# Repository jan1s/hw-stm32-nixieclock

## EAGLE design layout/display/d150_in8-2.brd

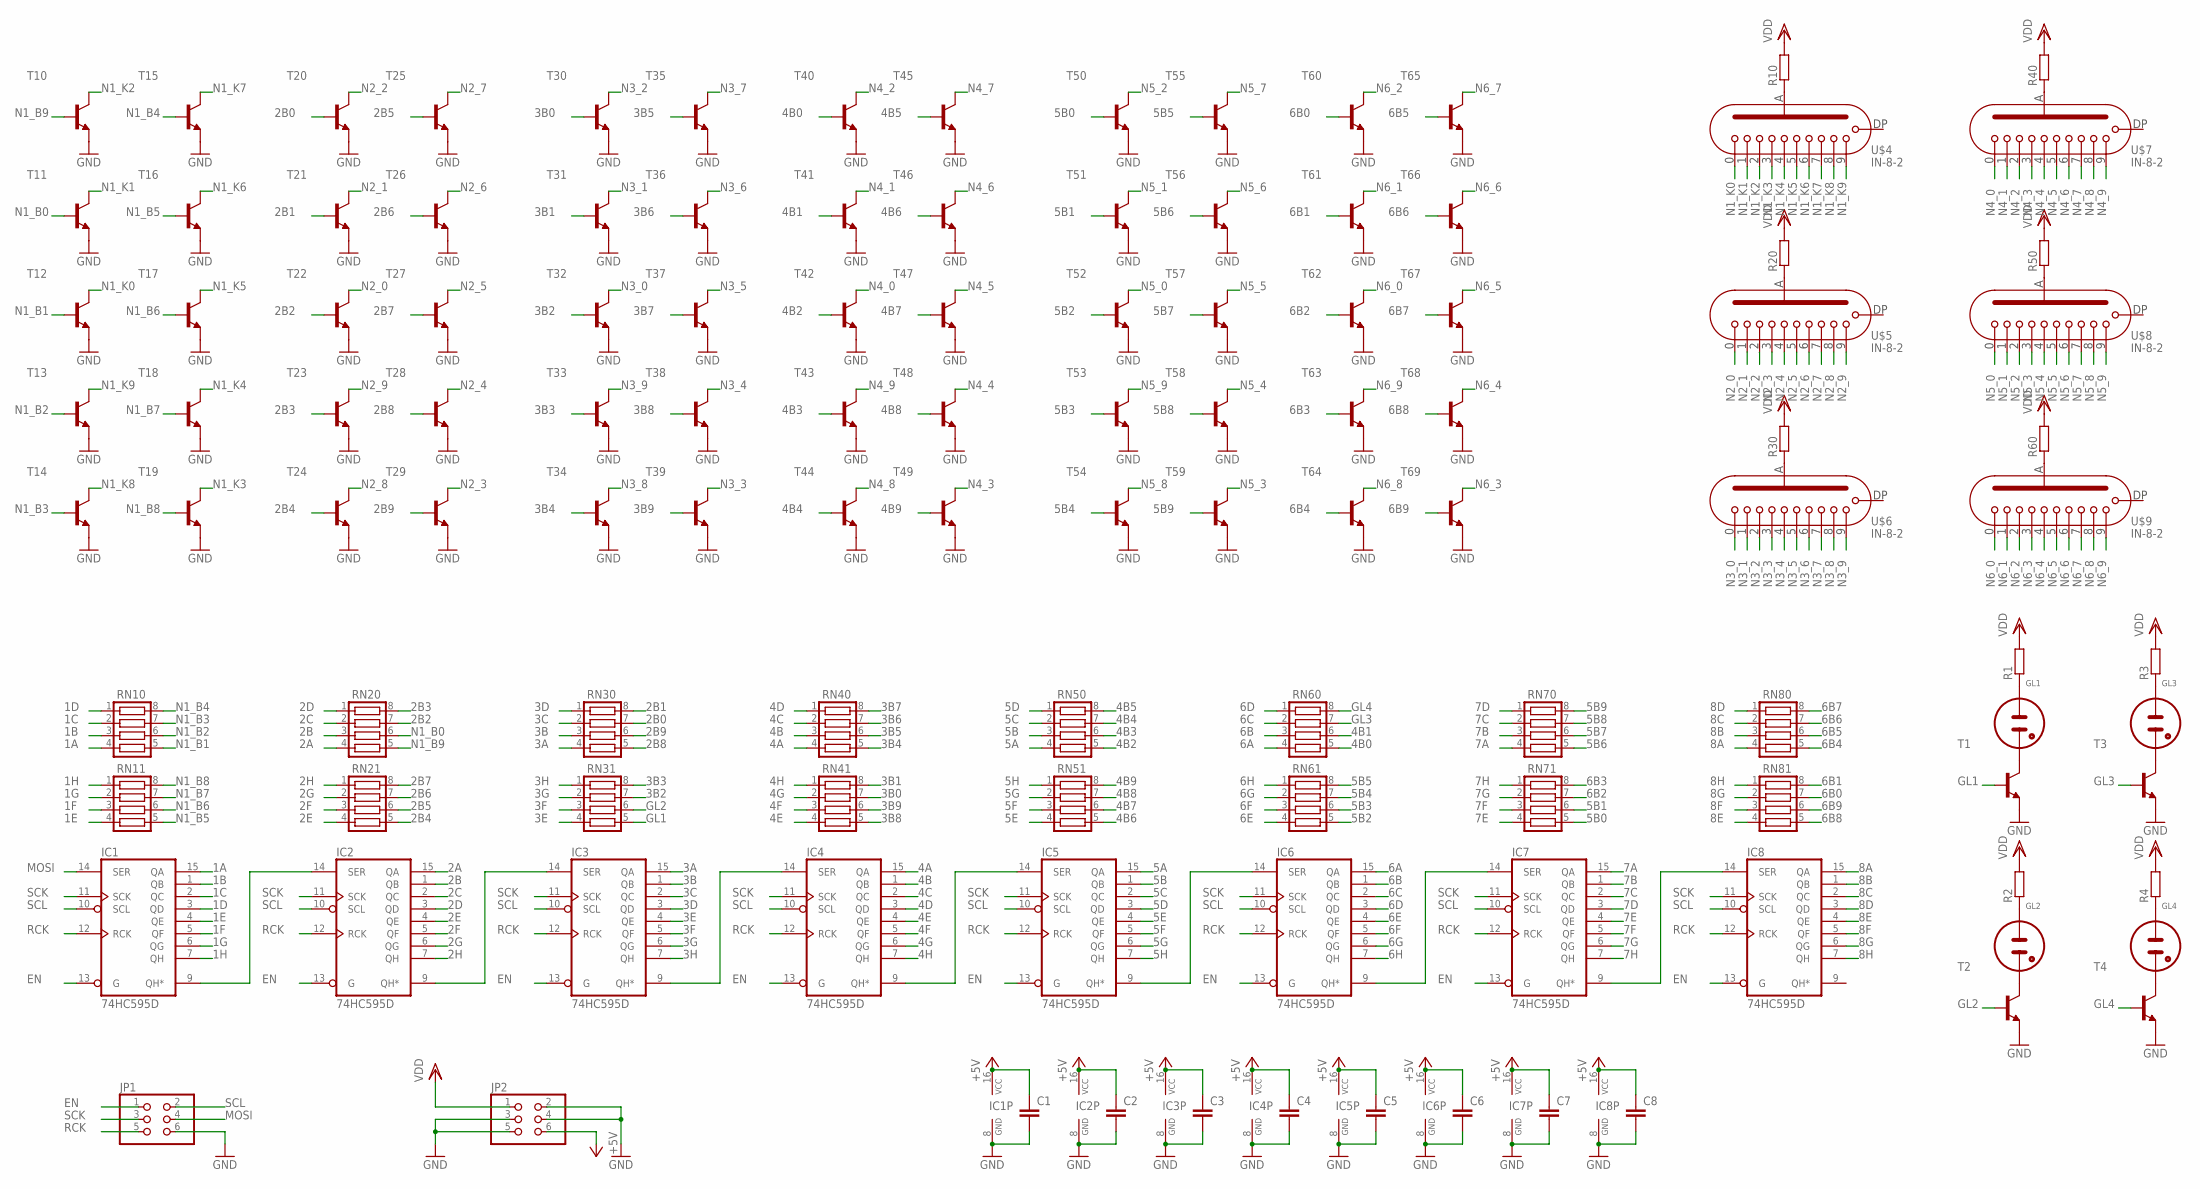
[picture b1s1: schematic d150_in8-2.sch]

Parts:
C1, C2, C3, C4, C5, C6, C7, C8: C-EUC0603; C0603
GL1, GL2, GL3, GL4: NE2-NEON-BULB-DRILL
IC1, IC2, IC3, IC4, IC5, IC6, IC7, IC8: 74HC595D; SO16
JP1, JP2: PINHD-2X3_2.54-SMD; 2X03SMD
R1, R2, R3, R4, R10, R20, R30, R40, R50, R60: R-EU_R0603; R0603
RN10, RN11, RN20, RN21, RN30, RN31, RN40, RN41, RN50, RN51, RN60, RN61, RN70, RN71, RN80, RN81: CTS742C083
T1, T2, T3, T4, T10, T11, T12, T13, T14, T15, T16, T17, T18, T19, T20, T21, T22, T23, T24, T25, T26, T27, T28, T29, T30, T31, T32, T33, T34, T35, T36, T37, T38, T39, T40, T41, T42, T43, T44, T45, T46, T47, T48, T49, T50, T51, T52, T53, T54, T55, T56, T57, T58, T59, T60, T61, T62, T63, T64, T65, T66, T67, T68, T69: SMBTA42; SOT23
U$4, U$5, U$6, U$7, U$8, U$9: IN-8-2

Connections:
1A: IC1.15 (QA), RN10.4
1B: IC1.1 (QB), RN10.3
1C: IC1.2 (QC), RN10.2
1D: IC1.3 (QD), RN10.1
1E: IC1.4 (QE), RN11.4
1F: IC1.5 (QF), RN11.3
1G: IC1.6 (QG), RN11.2
1H: IC1.7 (QH), RN11.1
2A: IC2.15 (QA), RN20.4
2B: IC2.1 (QB), RN20.3
2B0: RN30.7, T20.1 (B)
2B1: RN30.8, T21.1 (B)
2B2: RN20.7, T22.1 (B)
2B3: RN20.8, T23.1 (B)
2B4: RN21.5, T24.1 (B)
2B5: RN21.6, T25.1 (B)
2B6: RN21.7, T26.1 (B)
2B7: RN21.8, T27.1 (B)
2B8: RN30.5, T28.1 (B)
2B9: RN30.6, T29.1 (B)
2C: IC2.2 (QC), RN20.2
2D: IC2.3 (QD), RN20.1
2E: IC2.4 (QE), RN21.4
2F: IC2.5 (QF), RN21.3
2G: IC2.6 (QG), RN21.2
2H: IC2.7 (QH), RN21.1
3A: IC3.15 (QA), RN30.4
3B: IC3.1 (QB), RN30.3
3B0: RN41.7, T30.1 (B)
3B1: RN41.8, T31.1 (B)
3B2: RN31.7, T32.1 (B)
3B3: RN31.8, T33.1 (B)
3B4: RN40.5, T34.1 (B)
3B5: RN40.6, T35.1 (B)
3B6: RN40.7, T36.1 (B)
3B7: RN40.8, T37.1 (B)
3B8: RN41.5, T38.1 (B)
3B9: RN41.6, T39.1 (B)
3C: IC3.2 (QC), RN30.2
3D: IC3.3 (QD), RN30.1
3E: IC3.4 (QE), RN31.4
3F: IC3.5 (QF), RN31.3
3G: IC3.6 (QG), RN31.2
3H: IC3.7 (QH), RN31.1
4A: IC4.15 (QA), RN40.4
4B: IC4.1 (QB), RN40.3
4B0: RN60.5, T40.1 (B)
4B1: RN60.6, T41.1 (B)
4B2: RN50.5, T42.1 (B)
4B3: RN50.6, T43.1 (B)
4B4: RN50.7, T44.1 (B)
4B5: RN50.8, T45.1 (B)
4B6: RN51.5, T46.1 (B)
4B7: RN51.6, T47.1 (B)
4B8: RN51.7, T48.1 (B)
4B9: RN51.8, T49.1 (B)
4C: IC4.2 (QC), RN40.2
4D: IC4.3 (QD), RN40.1
4E: IC4.4 (QE), RN41.4
4F: IC4.5 (QF), RN41.3
4G: IC4.6 (QG), RN41.2
4H: IC4.7 (QH), RN41.1
5A: IC5.15 (QA), RN50.4
5B: IC5.1 (QB), RN50.3
5B0: RN71.5, T50.1 (B)
5B1: RN71.6, T51.1 (B)
5B2: RN61.5, T52.1 (B)
5B3: RN61.6, T53.1 (B)
5B4: RN61.7, T54.1 (B)
5B5: RN61.8, T55.1 (B)
5B6: RN70.5, T56.1 (B)
5B7: RN70.6, T57.1 (B)
5B8: RN70.7, T58.1 (B)
5B9: RN70.8, T59.1 (B)
5C: IC5.2 (QC), RN50.2
5D: IC5.3 (QD), RN50.1
5E: IC5.4 (QE), RN51.4
5F: IC5.5 (QF), RN51.3
5G: IC5.6 (QG), RN51.2
5H: IC5.7 (QH), RN51.1
6A: IC6.15 (QA), RN60.4
6B: IC6.1 (QB), RN60.3
6B0: RN81.7, T60.1 (B)
6B1: RN81.8, T61.1 (B)
6B2: RN71.7, T62.1 (B)
6B3: RN71.8, T63.1 (B)
6B4: RN80.5, T64.1 (B)
6B5: RN80.6, T65.1 (B)
6B6: RN80.7, T66.1 (B)
6B7: RN80.8, T67.1 (B)
6B8: RN81.5, T68.1 (B)
6B9: RN81.6, T69.1 (B)
6C: IC6.2 (QC), RN60.2
6D: IC6.3 (QD), RN60.1
6E: IC6.4 (QE), RN61.4
6F: IC6.5 (QF), RN61.3
6G: IC6.6 (QG), RN61.2
6H: IC6.7 (QH), RN61.1
7A: IC7.15 (QA), RN70.4
7B: IC7.1 (QB), RN70.3
7C: IC7.2 (QC), RN70.2
7D: IC7.3 (QD), RN70.1
7E: IC7.4 (QE), RN71.4
7F: IC7.5 (QF), RN71.3
7G: IC7.6 (QG), RN71.2
7H: IC7.7 (QH), RN71.1
8A: IC8.15 (QA), RN80.4
8B: IC8.1 (QB), RN80.3
8C: IC8.2 (QC), RN80.2
8D: IC8.3 (QD), RN80.1
8E: IC8.4 (QE), RN81.4
8F: IC8.5 (QF), RN81.3
8G: IC8.6 (QG), RN81.2
8H: IC8.7 (QH), RN81.1
+5V: C1.1, C2.1, C3.1, C4.1, C5.1, C6.1, C7.1, C8.1, IC1.16 (VCC), IC2.16 (VCC), IC3.16 (VCC), IC4.16 (VCC), IC5.16 (VCC), IC6.16 (VCC), IC7.16 (VCC), IC8.16 (VCC), JP2.6
EN: IC1.13 (G), IC2.13 (G), IC3.13 (G), IC4.13 (G), IC5.13 (G), IC6.13 (G), IC7.13 (G), IC8.13 (G), JP1.1
GL1: RN31.5, T1.1 (B)
GL2: RN31.6, T2.1 (B)
GL3: RN60.7, T3.1 (B)
GL4: RN60.8, T4.1 (B)
GND: C1.2, C2.2, C3.2, C4.2, C5.2, C6.2, C7.2, C8.2, IC1.8 (GND), IC2.8 (GND), IC3.8 (GND), IC4.8 (GND), IC5.8 (GND), IC6.8 (GND), IC7.8 (GND), IC8.8 (GND), JP1.6, JP2.2, JP2.3, JP2.4, JP2.5, T1.2 (E), T2.2 (E), T3.2 (E), T4.2 (E), T10.2 (E), T11.2 (E), T12.2 (E), T13.2 (E), T14.2 (E), T15.2 (E), T16.2 (E), T17.2 (E), T18.2 (E), T19.2 (E), T20.2 (E), T21.2 (E), T22.2 (E), T23.2 (E), T24.2 (E), T25.2 (E), T26.2 (E), T27.2 (E), T28.2 (E), T29.2 (E), T30.2 (E), T31.2 (E), T32.2 (E), T33.2 (E), T34.2 (E), T35.2 (E), T36.2 (E), T37.2 (E), T38.2 (E), T39.2 (E), T40.2 (E), T41.2 (E), T42.2 (E), T43.2 (E), T44.2 (E), T45.2 (E), T46.2 (E), T47.2 (E), T48.2 (E), T49.2 (E), T50.2 (E), T51.2 (E), T52.2 (E), T53.2 (E), T54.2 (E), T55.2 (E), T56.2 (E), T57.2 (E), T58.2 (E), T59.2 (E), T60.2 (E), T61.2 (E), T62.2 (E), T63.2 (E), T64.2 (E), T65.2 (E), T66.2 (E), T67.2 (E), T68.2 (E), T69.2 (E)
MOSI: IC1.14 (SER), JP1.4
N1_B0: RN20.6, T11.1 (B)
N1_B1: RN10.5, T12.1 (B)
N1_B2: RN10.6, T13.1 (B)
N1_B3: RN10.7, T14.1 (B)
N1_B4: RN10.8, T15.1 (B)
N1_B5: RN11.5, T16.1 (B)
N1_B6: RN11.6, T17.1 (B)
N1_B7: RN11.7, T18.1 (B)
N1_B8: RN11.8, T19.1 (B)
N1_B9: RN20.5, T10.1 (B)
N1_K0: T12.3 (C), U$4.0
N1_K1: T11.3 (C), U$4.1
N1_K2: T10.3 (C), U$4.2
N1_K3: T19.3 (C), U$4.3
N1_K4: T18.3 (C), U$4.4
N1_K5: T17.3 (C), U$4.5
N1_K6: T16.3 (C), U$4.6
N1_K7: T15.3 (C), U$4.7
N1_K8: T14.3 (C), U$4.8
N1_K9: T13.3 (C), U$4.9
N2_0: T22.3 (C), U$5.0
N2_1: T21.3 (C), U$5.1
N2_2: T20.3 (C), U$5.2
N2_3: T29.3 (C), U$5.3
N2_4: T28.3 (C), U$5.4
N2_5: T27.3 (C), U$5.5
N2_6: T26.3 (C), U$5.6
N2_7: T25.3 (C), U$5.7
N2_8: T24.3 (C), U$5.8
N2_9: T23.3 (C), U$5.9
N3_0: T32.3 (C), U$6.0
N3_1: T31.3 (C), U$6.1
N3_2: T30.3 (C), U$6.2
N3_3: T39.3 (C), U$6.3
N3_4: T38.3 (C), U$6.4
N3_5: T37.3 (C), U$6.5
N3_6: T36.3 (C), U$6.6
N3_7: T35.3 (C), U$6.7
N3_8: T34.3 (C), U$6.8
N3_9: T33.3 (C), U$6.9
N4_0: T42.3 (C), U$7.0
N4_1: T41.3 (C), U$7.1
N4_2: T40.3 (C), U$7.2
N4_3: T49.3 (C), U$7.3
N4_4: T48.3 (C), U$7.4
N4_5: T47.3 (C), U$7.5
N4_6: T46.3 (C), U$7.6
N4_7: T45.3 (C), U$7.7
N4_8: T44.3 (C), U$7.8
N4_9: T43.3 (C), U$7.9
N5_0: T52.3 (C), U$8.0
N5_1: T51.3 (C), U$8.1
N5_2: T50.3 (C), U$8.2
N5_3: T59.3 (C), U$8.3
N5_4: T58.3 (C), U$8.4
N5_5: T57.3 (C), U$8.5
N5_6: T56.3 (C), U$8.6
N5_7: T55.3 (C), U$8.7
N5_8: T54.3 (C), U$8.8
N5_9: T53.3 (C), U$8.9
N6_0: T62.3 (C), U$9.0
N6_1: T61.3 (C), U$9.1
N6_2: T60.3 (C), U$9.2
N6_3: T69.3 (C), U$9.3
N6_4: T68.3 (C), U$9.4
N6_5: T67.3 (C), U$9.5
N6_6: T66.3 (C), U$9.6
N6_7: T65.3 (C), U$9.7
N6_8: T64.3 (C), U$9.8
N6_9: T63.3 (C), U$9.9
unnamed: GL2.1 (A), R2.1
unnamed: GL3.1 (A), R3.1
unnamed: GL4.1 (A), R4.1
unnamed: R10.1, U$4.A (A1)
unnamed: GL2.2 (A1), T2.3 (C)
unnamed: GL1.2 (A1), T1.3 (C)
unnamed: GL4.2 (A1), T4.3 (C)
unnamed: GL3.2 (A1), T3.3 (C)
unnamed: R20.1, U$5.A (A1)
unnamed: IC1.9 (QH*), IC2.14 (SER)
unnamed: IC2.9 (QH*), IC3.14 (SER)
unnamed: IC3.9 (QH*), IC4.14 (SER)
unnamed: R30.1, U$6.A (A1)
unnamed: R40.1, U$7.A (A1)
unnamed: R50.1, U$8.A (A1)
unnamed: IC4.9 (QH*), IC5.14 (SER)
unnamed: R60.1, U$9.A (A1)
unnamed: IC5.9 (QH*), IC6.14 (SER)
unnamed: IC6.9 (QH*), IC7.14 (SER)
unnamed: IC7.9 (QH*), IC8.14 (SER)
unnamed: GL1.1 (A), R1.1
RCK: IC1.12 (RCK), IC2.12 (RCK), IC3.12 (RCK), IC4.12 (RCK), IC5.12 (RCK), IC6.12 (RCK), IC7.12 (RCK), IC8.12 (RCK), JP1.5
SCK: IC1.11 (SCK), IC2.11 (SCK), IC3.11 (SCK), IC4.11 (SCK), IC5.11 (SCK), IC6.11 (SCK), IC7.11 (SCK), IC8.11 (SCK), JP1.3
SCL: IC1.10 (SCL), IC2.10 (SCL), IC3.10 (SCL), IC4.10 (SCL), IC5.10 (SCL), IC6.10 (SCL), IC7.10 (SCL), IC8.10 (SCL), JP1.2
VDD: JP2.1, R1.2, R2.2, R3.2, R4.2, R10.2, R20.2, R30.2, R40.2, R50.2, R60.2

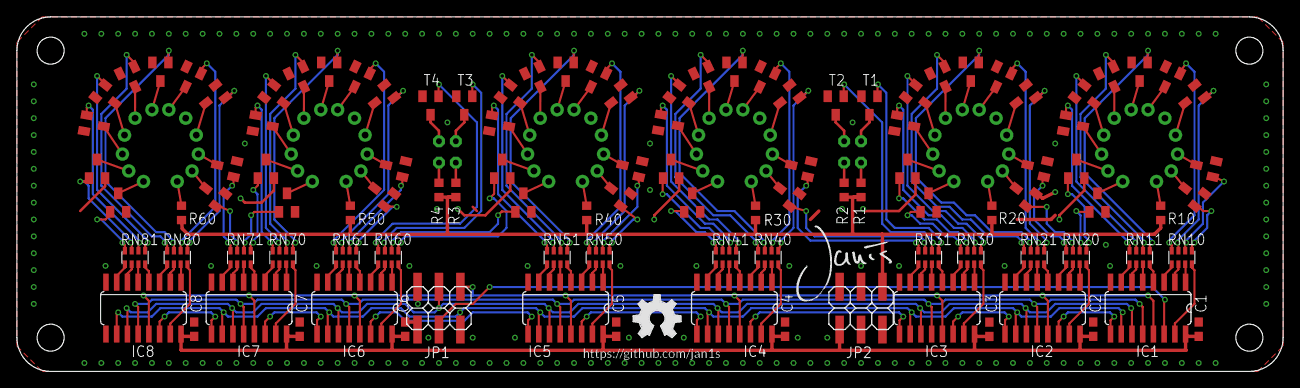
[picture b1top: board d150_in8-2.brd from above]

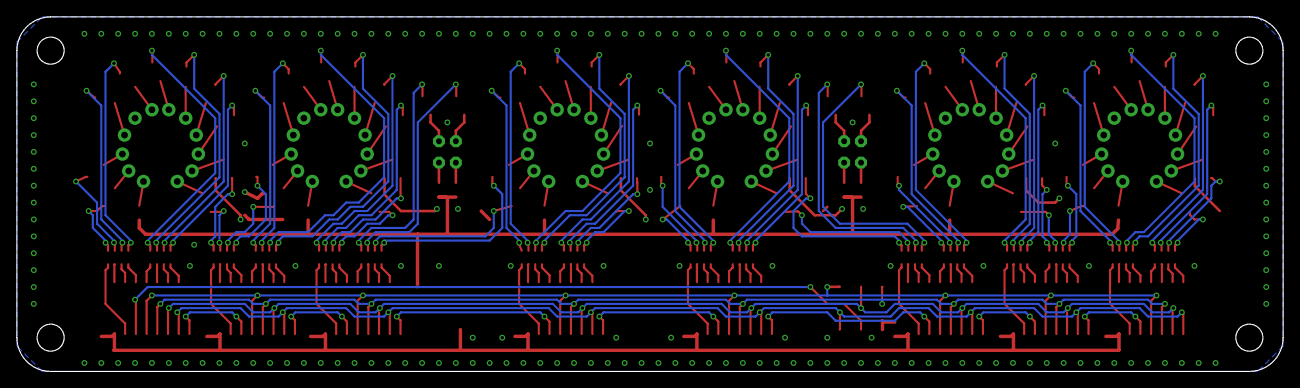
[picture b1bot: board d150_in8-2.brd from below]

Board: 2 copper layers, 150.0 x 42.0 mm, 121 parts (10 on the bottom side), 217 nets.

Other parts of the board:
U$1: OSHW_FILLX200_NOTEXT
U$2: JANIS_10MM
U$3: GITHUB/JAN1S
